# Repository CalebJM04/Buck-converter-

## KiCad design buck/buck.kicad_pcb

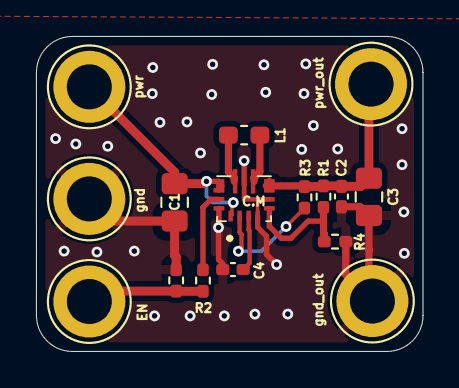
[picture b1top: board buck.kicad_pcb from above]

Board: 2 copper layers, 21.5 x 17.5 mm, 16 parts (0 on the bottom side), 10 nets.

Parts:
C1, C3: 47uF; C_0805_2012Metric_Pad1.18x1.45mm_HandSolder
C2: 10uF; C_0402_1005Metric_Pad0.74x0.62mm_HandSolder
C4: 100nF; C_0402_1005Metric_Pad0.74x0.62mm_HandSolder
EN: EN; TestPoint_Loop_D3.80mm_Drill2.5mm
IC1: TPS630702RNMR; TPS630701RNMR
L1: 1.5uH; L_0603_1608Metric_Pad1.05x0.95mm_HandSolder
R1: 309k; R_0402_1005Metric_Pad0.72x0.64mm_HandSolder
R2: 10k; R_0402_1005Metric_Pad0.72x0.64mm_HandSolder
R3, R4: 100k; R_0402_1005Metric_Pad0.72x0.64mm_HandSolder
R5: 0; R_0402_1005Metric_Pad0.72x0.64mm_HandSolder
gnd: gnd; TestPoint_Loop_D3.80mm_Drill2.5mm
gnd_out: pwr; TestPoint_Loop_D3.80mm_Drill2.5mm
pwr: pwr; TestPoint_Loop_D3.80mm_Drill2.5mm
pwr_out: gnd; TestPoint_Loop_D3.80mm_Drill2.5mm

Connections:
+3.3V: C2.1, C3.1, IC1.7 (VOUT_1), IC1.8 (VOUT_2), IC1.17 (VOUT_1), R1.2, R3.2, pwr_out.1
GND: C1.2, C2.2, C3.2, C4.2, IC1.4 (GND), IC1.6 (FB2), IC1.10 (PGND), IC1.15 (VSEL), R4.1, R5.2, gnd.1, gnd_out.1
unnamed: EN.1, R2.1, R5.1
unnamed: IC1.14 (EN), R2.2
unnamed: IC1.5 (FB), R1.1, R4.2
unnamed: IC1.11 (L1), L1.1
unnamed: IC1.9 (L2), L1.2
unnamed: IC1.2 (PG), R3.1
unnamed: C1.1, IC1.1 (PS/SYNC), IC1.12 (VIN_1), IC1.13 (VIN_2), IC1.16 (VIN_2), pwr.1
unnamed: C4.1, IC1.3 (VAUX)

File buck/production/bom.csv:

Designator,Footprint,Quantity,Value,LCSC Part #
"C1, C3",0805,2,47uF,
C2,0402,1,10uF,
C4,0402,1,100nF,
EN1,TestPoint_THTPad_1.0x1.0mm_Drill0.5mm,1,EN,
"GND, PWR_OUT",TestPoint_THTPad_1.0x1.0mm_Drill0.5mm,2,gnd,
"GND_OUT, PWR1",TestPoint_THTPad_1.0x1.0mm_Drill0.5mm,2,pwr,
IC1,TPS630701RNMR,1,TPS630702RNMR,
L1,0603,1,1.5uH,
R1,0402,1,309k,
R2,0402,1,10k,
"R3, R4",0402,2,100k,

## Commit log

2025-09-11 first rev (finished?)
    pretty simple. nothing crazy. side square is a comparison to the seeed studio esp32 since that's also being used
2025-09-11 made prod file
2025-09-12 add through hole solder spots as per request
2025-09-12 removed esp32 comp
2025-09-12 dorked around
2025-09-14 slight fixes
2025-09-17 made prod, gave components for everything
2025-09-17 made prod with through hole mounts
2025-11-08 redesigned with new en tie to gnd and 4x pads
    added name under IC and near back of board
2025-11-08 made prod. sent to simon
2025-11-08 sent pics to simon
